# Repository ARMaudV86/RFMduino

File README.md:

# RFMduino
Small RF development board based on ATMEGA328PB and RMF22 / RFM69HCW

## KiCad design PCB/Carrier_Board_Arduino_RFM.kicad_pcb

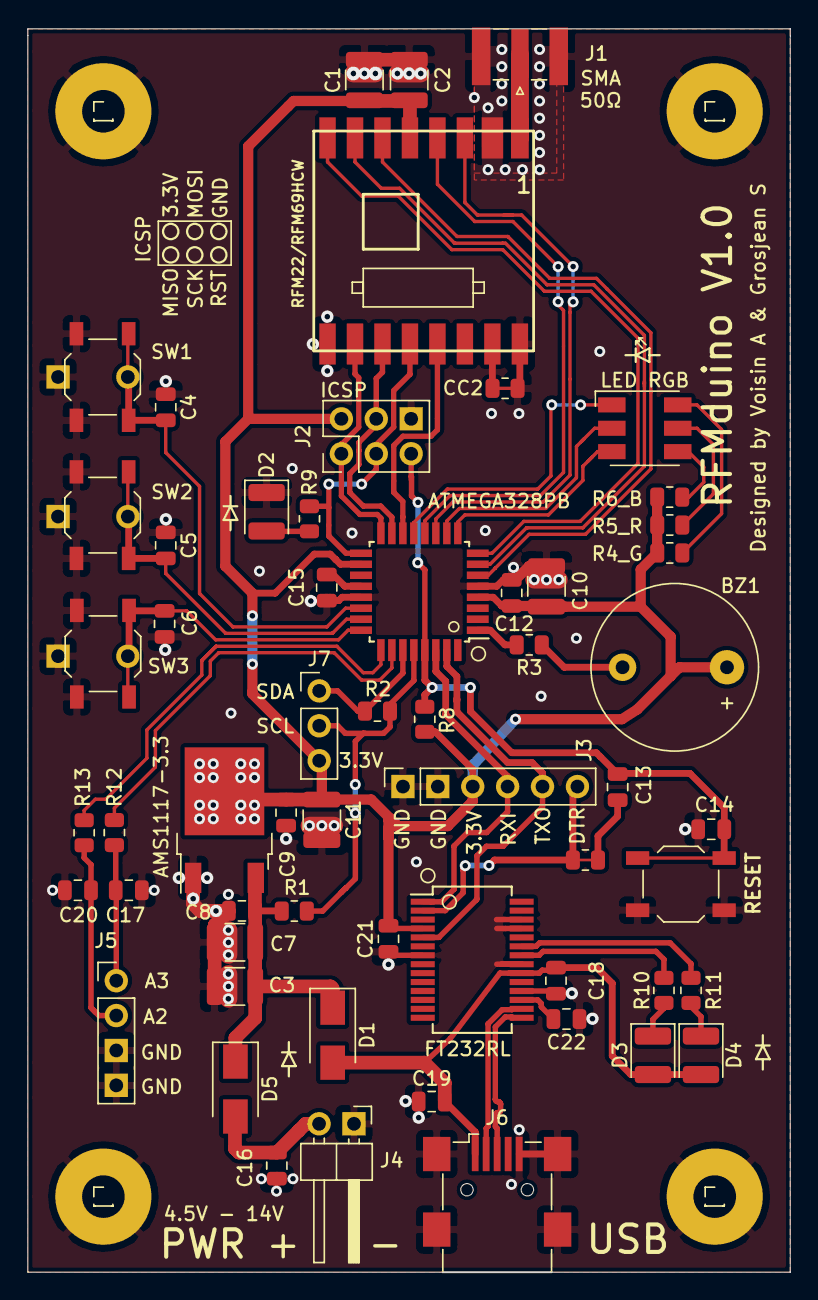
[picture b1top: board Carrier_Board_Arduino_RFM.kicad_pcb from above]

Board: 2 copper layers, 55.5 x 90.5 mm, 64 parts (0 on the bottom side), 45 nets.

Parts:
AMS1117-3.3: AMS1117-3.3; TO-252-2
ATMEGA328PB: ATMEGA328PB; TQFP-32_7x7mm_P0.8mm
BZ1: Buzzer; Buzzer_12x9.5RM7.6
C1, C3, C10: DNP; C_1210_3225Metric
C2, C7, C11: 10uF; C_1210_3225Metric
C4, C5, C6, C12, C13, C14, C16, C17, C18, C19, C20: 0.1uF; C_0805_2012Metric
C8, C9, C21, C22: DNP; C_0805_2012Metric
C15: DNP/0.1uF; C_0805_2012Metric
CC2, CC3: R; R_0805_2012Metric
D1, D5: D_Schottky; D_SMA
D2, D3, D4: LED; LED_1210_3225Metric
FT232RL: FT232RL; SSOP-28_5.3x10.2mm_P0.65mm
J1: Conn_Coaxial; SMA_Samtec_SMA-J-P-X-ST-EM1_EdgeMount
J2: ICSP; PinHeader_2x03_P2.54mm_Vertical
J3: FTDI; PinSocket_1x06_P2.54mm_Vertical
J4: Connecteur_Batterie; PinHeader_1x02_P2.54mm_Horizontal
J5: EXT_IO; PinHeader_1x04_P2.54mm_Vertical
J6: USB_B_Mini; USB_Mini-B_Wuerth_65100516121_Horizontal
J7: I2C; PinHeader_1x03_P2.54mm_Vertical
J8: BUTTON 0; PinSocket_1x01_P2.54mm_Vertical
J9: BUTTON 1; PinSocket_1x01_P2.54mm_Vertical
J10: BUTTON 2; PinSocket_1x01_P2.54mm_Vertical
J11, J12, J13: GND; PinSocket_1x01_P2.54mm_Vertical
LED RGB: LED_RGB; LED_RGB_5050-6
R1, R2, R3, R12, R13: DNP; R_0805_2012Metric
R4_G: 120; R_0805_2012Metric
R5_R: 330; R_0805_2012Metric
R6_B: 1500; R_0805_2012Metric
R8: 10k; R_0805_2012Metric
R9: 220; R_0805_2012Metric
R10, R11: 270; R_0805_2012Metric
RESET: SW_MEC_5E; Push-Button
RFM22/RFM69HCW: RFM22
SW1: BUTTON_0; Push-Button
SW2: BUTTON_1; Push-Button
SW3: BUTTON_2; Push-Button

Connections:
3.3V: AMS1117-3.3.2, ATMEGA328PB.4, ATMEGA328PB.18, BZ1.1, C1.1, C2.1, C9.1, C10.1, C11.1, C12.1, C21.2, FT232RL.4, J2.2, J3.3, J7.3, R4_G.1, R5_R.1, R6_B.1, R8.1, RFM22/RFM69HCW.5
5V_USB: C18.2, C19.2, D1.2, D3.2, D4.2, FT232RL.20, J6.1
BATT: C16.2, D5.2, J4.2
BUTTON_0: ATMEGA328PB.22, C4.2, J8.1, SW1.1, SW1.2
BUTTON_1: ATMEGA328PB.23, C5.2, J9.1, SW2.1, SW2.2
BUTTON_2: ATMEGA328PB.24, C6.2, J10.1, SW3.1, SW3.2
BUZZER: ATMEGA328PB.1, R3.2
DTR: C13.1, CC3.1, CC3.2, FT232RL.2, J3.6
EXT_IO_0: ATMEGA328PB.25, R13.2
EXT_IO_1: ATMEGA328PB.26, R12.2
GND: AMS1117-3.3.1, ATMEGA328PB.5, ATMEGA328PB.21, C1.2, C2.2, C3.2, C4.1, C5.1, C6.1, C7.2, C8.2, C9.2, C10.2, C11.2, C12.2, C14.1, C15.2, C16.1, C17.1, C18.1, C19.1, C20.1, C21.1, C22.1, CC2.1, D2.1, FT232RL.7, FT232RL.18, FT232RL.21, FT232RL.25, FT232RL.26, J1.2, J2.6, J3.1, J3.2, J4.1, J5.3, J5.4, J6.5, J6.6, J11.1, J12.1, J13.1, RESET.3, RESET.4, RFM22/RFM69HCW.2, RFM22/RFM69HCW.9, RFM22/RFM69HCW.16, SW1.3, SW1.4, SW2.3, SW2.4, SW3.3, SW3.4
GPIO_0: ATMEGA328PB.6, RFM22/RFM69HCW.6
GPIO_1: ATMEGA328PB.7, RFM22/RFM69HCW.7
GPIO_2: ATMEGA328PB.8, RFM22/RFM69HCW.8
IN_M: ATMEGA328PB.28, J7.2, R1.2, R2.2
IN_M_ENABLE: ATMEGA328PB.27, J7.1, R2.1
LED_1: ATMEGA328PB.9, LED RGB.3
LED_2: ATMEGA328PB.10, LED RGB.2
LED_3: ATMEGA328PB.13, LED RGB.1
MISO: ATMEGA328PB.16, J2.1, RFM22/RFM69HCW.10
MOSI: ATMEGA328PB.15, J2.4, RFM22/RFM69HCW.11
unnamed: AMS1117-3.3.3, C3.1, C7.1, C8.1, D1.1, D5.1, R1.1
unnamed: ATMEGA328PB.20, C15.1
unnamed: BZ1.2, R3.1
unnamed: C17.2, J5.1, R12.1
unnamed: C20.2, J5.2, R13.1
unnamed: C22.2, FT232RL.17
unnamed: D2.2, R9.1
unnamed: D3.1, R10.2
unnamed: D4.1, R11.2
unnamed: FT232RL.22, R10.1
unnamed: FT232RL.23, R11.1
unnamed: J1.1, RFM22/RFM69HCW.1
unnamed: LED RGB.4, R6_B.2
unnamed: LED RGB.5, R5_R.2
unnamed: LED RGB.6, R4_G.2
RESET: ATMEGA328PB.29, C13.2, C14.2, J2.5, R8.2, RESET.1, RESET.2
RXI: ATMEGA328PB.30, FT232RL.1, J3.4
RX_Ant: ATMEGA328PB.11, RFM22/RFM69HCW.3
SCK: ATMEGA328PB.17, J2.3, R9.2, RFM22/RFM69HCW.12
SS: ATMEGA328PB.14, RFM22/RFM69HCW.13
TXO: ATMEGA328PB.31, FT232RL.5, J3.5
TX_Ant: ATMEGA328PB.12, RFM22/RFM69HCW.4
USB+: FT232RL.15, J6.3
USB-: FT232RL.16, J6.2

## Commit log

2020-11-29 Create LICENSE
